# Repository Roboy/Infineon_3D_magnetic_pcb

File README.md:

# Infineon 3D magnetic sensor boards

## 3D_magnetic_board

## Tactile_Skin_Board

## 3D_magnetic_board_small

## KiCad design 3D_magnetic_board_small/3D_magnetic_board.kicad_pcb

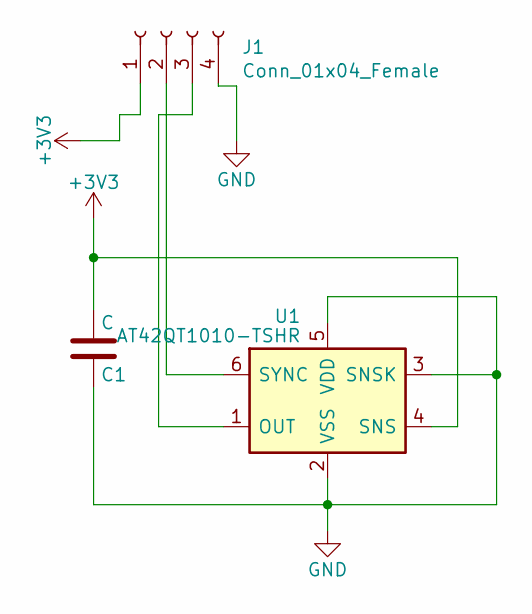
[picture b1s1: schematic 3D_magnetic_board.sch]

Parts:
C1: C; C_0402
J1: Conn_01x04_Female; PinHeader_1x04_P1.00mm_Horizontal
U1: AT42QT1010-TSHR; TSOP-6

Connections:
+3V3: C1.2, J1.1, U1.4 (SNS)
GND: C1.1, J1.4, U1.2 (VSS), U1.3 (SNSK), U1.5 (VDD)
unnamed: J1.2, U1.6 (SYNC)
unnamed: J1.3, U1.1 (OUT)

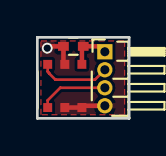
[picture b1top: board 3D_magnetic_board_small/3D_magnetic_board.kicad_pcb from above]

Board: 2 copper layers, 5.1 x 4.5 mm, 3 parts (0 on the bottom side), 4 nets.

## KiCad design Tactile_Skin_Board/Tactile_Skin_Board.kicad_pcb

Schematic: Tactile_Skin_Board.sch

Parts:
C1, C2, C3, C4, C5, C6, C7, C8, C9: C; C_0402_1005Metric
J1: Conn_02x09_Odd_Even_Shielded; PinHeader_2x09_P2.54mm_Vertical
J2: Conn_01x02_Female; PinHeader_1x02_P2.54mm_Vertical
R1, R2, R3, R4, R5, R6, R7, R8, R9, R10, R11, R12, R13, R14, R15, R16, R17, R18: R; R_01005_0402Metric
U1, U2, U3, U4, U5, U6, U7, U8, U9: AT42QT1010-TSHR; SOT-23-6

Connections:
3.3V: C1.2, C2.2, C3.2, C4.2, C5.2, C6.2, C7.2, C8.2, C9.2, J2.2, U1.4 (SNS), U2.4 (SNS), U3.4 (SNS), U4.4 (SNS), U5.4 (SNS), U6.4 (SNS), U7.4 (SNS), U8.4 (SNS), U9.4 (SNS)
GND: C1.1, C2.1, C3.1, C4.1, C5.1, C6.1, C7.1, C8.1, C9.1, J2.1, R1.1, R2.1, R3.1, R4.1, R5.1, R6.1, R7.1, R8.1, R9.1, R10.1, R11.1, R12.1, R13.1, R14.1, R15.1, R16.1, R17.1, R18.1, U1.2 (VSS), U1.3 (SNSK), U1.5 (VDD), U2.2 (VSS), U2.3 (SNSK), U2.5 (VDD), U3.2 (VSS), U3.3 (SNSK), U3.5 (VDD), U4.2 (VSS), U4.3 (SNSK), U4.5 (VDD), U5.2 (VSS), U5.3 (SNSK), U5.5 (VDD), U6.2 (VSS), U6.3 (SNSK), U6.5 (VDD), U7.2 (VSS), U7.3 (SNSK), U7.5 (VDD), U8.2 (VSS), U8.3 (SNSK), U8.5 (VDD), U9.2 (VSS), U9.3 (SNSK), U9.5 (VDD)
SCL0: J1.2, R1.2, U1.1 (OUT)
SCL1: J1.4, R2.2, U2.1 (OUT)
SCL2: J1.6, R3.2, U3.1 (OUT)
SCL3: J1.8, R7.2, U4.1 (OUT)
SCL4: J1.10, R8.2, U5.1 (OUT)
SCL5: J1.12, R9.2, U6.1 (OUT)
SCL6: J1.14, R13.2, U7.1 (OUT)
SCL7: J1.16, R14.2, U8.1 (OUT)
SCL8: J1.18, R15.2, U9.1 (OUT)
SDA0: J1.1, R4.2, U1.6 (SYNC)
SDA1: J1.3, R5.2, U2.6 (SYNC)
SDA2: J1.5, R6.2, U3.6 (SYNC)
SDA3: J1.7, R10.2, U4.6 (SYNC)
SDA4: J1.9, R11.2, U5.6 (SYNC)
SDA5: J1.11, R12.2, U6.6 (SYNC)
SDA6: J1.13, R16.2, U7.6 (SYNC)
SDA7: J1.15, R17.2, U8.6 (SYNC)
SDA8: J1.17, R18.2, U9.6 (SYNC)

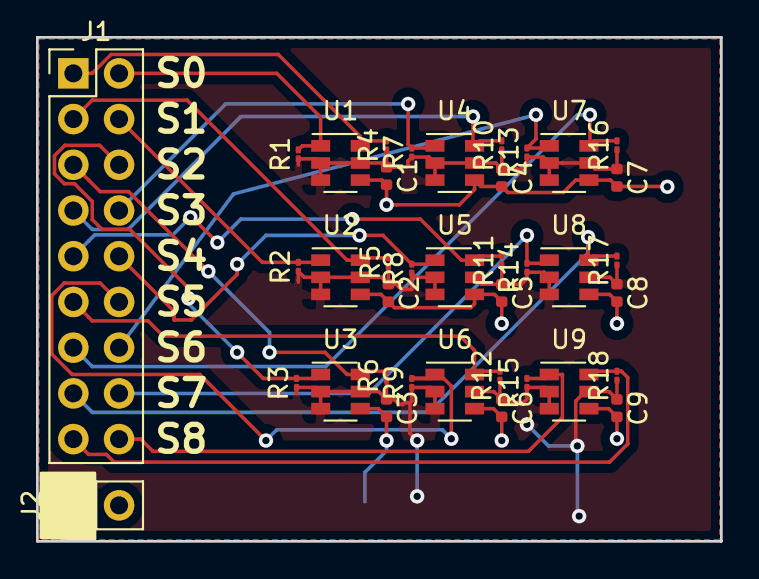
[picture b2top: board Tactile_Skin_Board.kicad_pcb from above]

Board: 2 copper layers, 38.0 x 28.0 mm, 39 parts (1 on the bottom side), 20 nets.

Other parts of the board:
svg2mod: G***; Roboy_big(4cm)_without_circle

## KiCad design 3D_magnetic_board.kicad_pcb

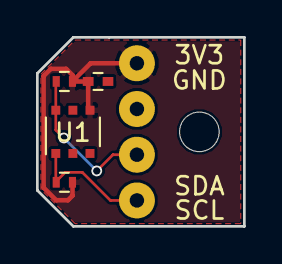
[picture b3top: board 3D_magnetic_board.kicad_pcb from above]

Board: 2 copper layers, 11.5 x 10.5 mm, 8 parts (0 on the bottom side), 4 nets.

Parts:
3V3: VDD; SolderWirePad_single_0-8mmDrill
C1: C; C_0402
GND: GND; SolderWirePad_single_0-8mmDrill
R1, R2: 10k; R_0402
SCL: SCL; SolderWirePad_single_0-8mmDrill
SDA: SDA; SolderWirePad_single_0-8mmDrill
U1: AT42QT1010-TSHR; TSOP-6

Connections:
+3V3: 3V3.1, C1.2, R1.1, R2.1, U1.4
GND: C1.1, GND.1, U1.2, U1.3, U1.5
unnamed: R2.2, SCL.1, U1.1
unnamed: R1.2, SDA.1, U1.6

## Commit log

2017-07-06 Initial commit, first small square board
2017-07-22 Started final pcb design, basic measurements are now fixed
2017-07-30 Corrected drill hole alignment and exchanged U1's footprint with the correct one.
2018-01-08 Added pullup resistors for I2C (optional placement), finished routing and preparing for manufacture. Board thickness 1mm.
2018-01-09 with panel
2018-01-10 v-cut min length as requested by pcbway is 75mm
2018-01-16 6x6 panel is minimum size for pcbway
2018-01-27 2x3 panel, fixed filled zones
2018-09-09 draft tactile skin
2019-03-02 smaller version
2019-03-02 with image
